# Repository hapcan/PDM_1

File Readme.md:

PDM
============

POWER DISTRIBUTION MODULE

Device webpage: http://hapcan.com/devices/universal/univ_3/pdm_1/

Hardware created in Eagle PCB Software http://www.cadsoftusa.com/

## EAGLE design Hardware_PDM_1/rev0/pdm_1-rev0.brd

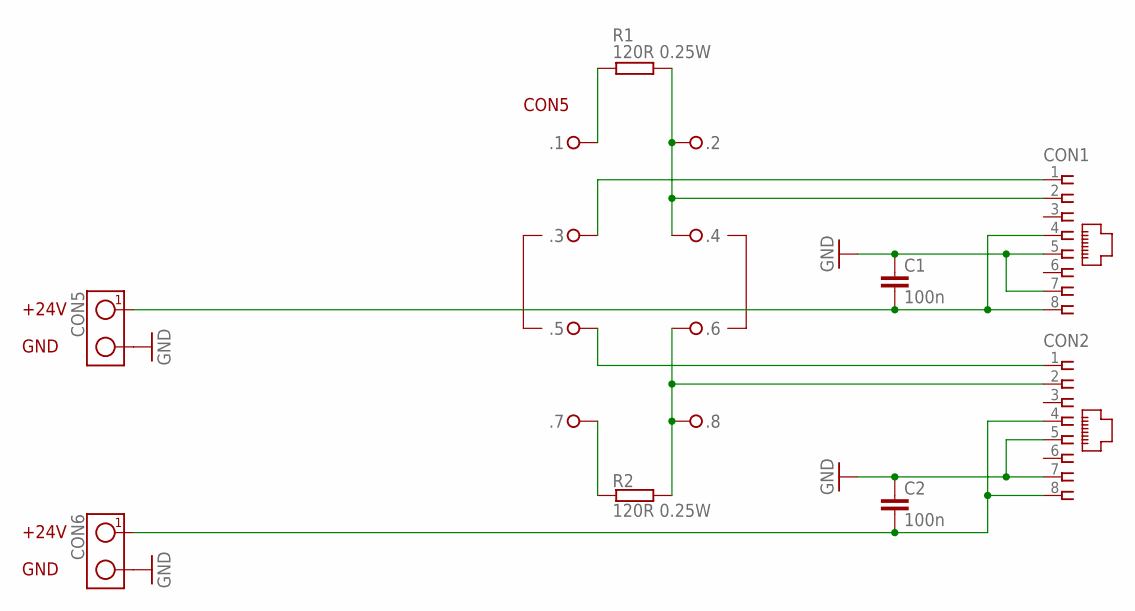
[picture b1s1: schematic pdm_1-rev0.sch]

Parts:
.: 2x4; HEADER-2X4
C1, C2: 100n; 0805
CON1, CON2: RJ45-SOCKET; RJ45-PCB-SOCKET
CON5, CON6: TERMINAL-2-7.5X10.5MM; ARK2-7.5X10.5MM
R1, R2: 120R 0.25W; 2010

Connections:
GND: C1.1, C2.1, CON1.5, CON1.7, CON2.5, CON2.7, CON5.2, CON6.2
unnamed: ..3, CON1.1
unnamed: ..2, ..4, CON1.2, R1.2
unnamed: ..5, CON2.1
unnamed: C1.2, CON1.4, CON1.8, CON5.1
unnamed: ..1, R1.1
unnamed: ..7, R2.1
unnamed: C2.2, CON2.4, CON2.8, CON6.1
unnamed: ..6, ..8, CON2.2, R2.2

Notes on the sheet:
+24V
GND
CON5

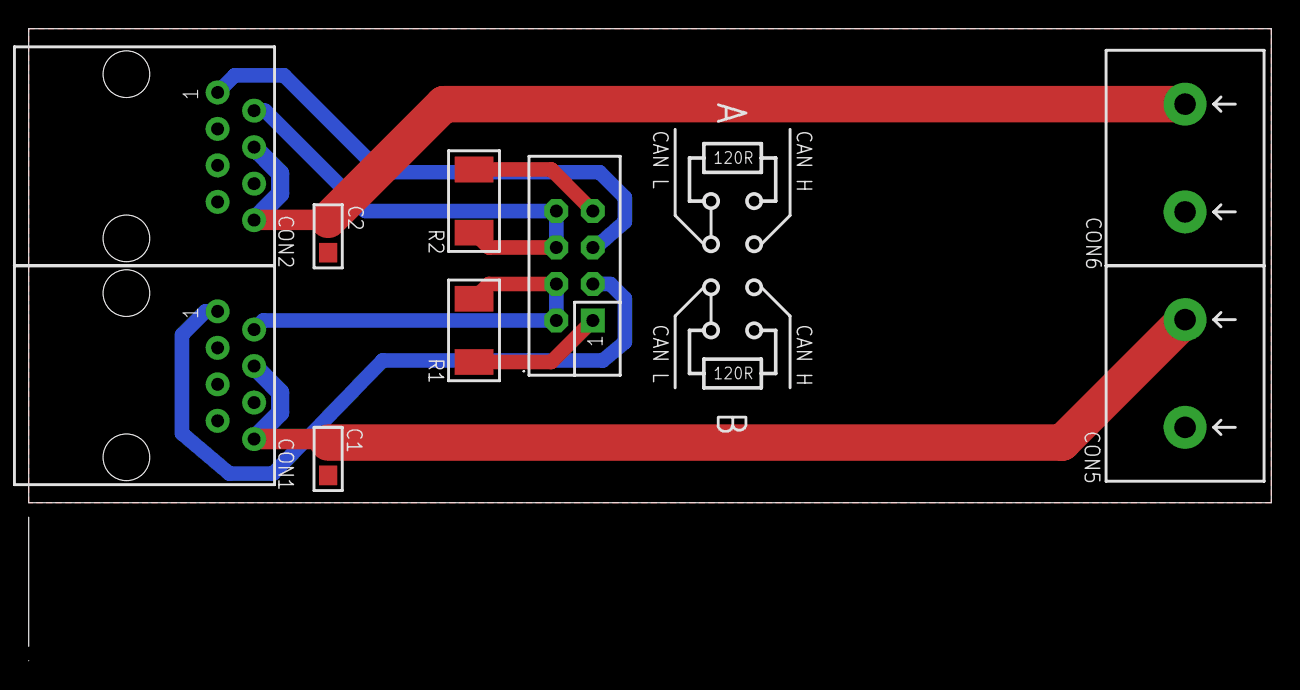
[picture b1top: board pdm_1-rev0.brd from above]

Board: 2 copper layers, 86.5 x 44.0 mm, 9 parts (0 on the bottom side), 9 nets.

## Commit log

2016-05-08 :lollipop: Added .gitattributes & .gitignore files
2016-05-08 hardware PDM 1 revision 0
